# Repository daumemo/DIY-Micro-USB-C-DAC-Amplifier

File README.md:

# DIY-Micro-USB-C-DAC-Amplifier
A DIY headphone amplifier based on INA1620 and USB-C DAC

Here you will find all Hardware files for my DIY micro headphone amplifier.

More information you can find at my site: https://daumemo.com/diy-micro-usb-c-to-3-5mm-adapter-and-headphone-amplifier-part-4/

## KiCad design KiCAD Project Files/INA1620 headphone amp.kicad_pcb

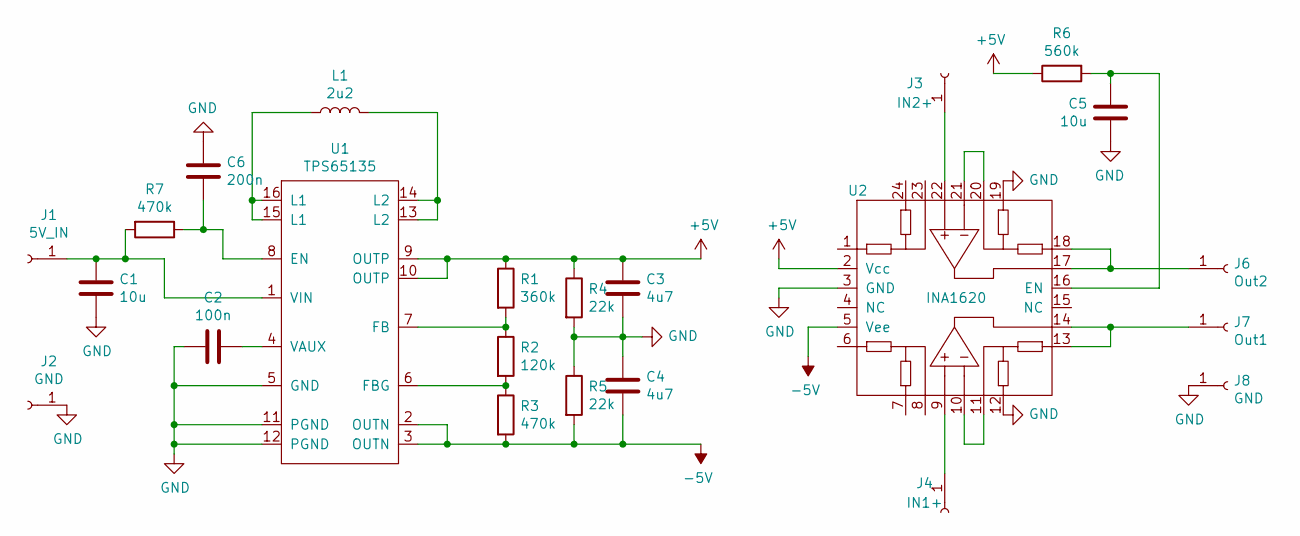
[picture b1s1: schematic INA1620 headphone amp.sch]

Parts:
C1, C5: 10u; C_0603_1608Metric
C2: 100n; C_0402_1005Metric
C3, C4: 4u7; C_0603_1608Metric
C6: 200n; C_0402_1005Metric
J1: 5V_IN; TestPoint_Pad_1.5x1.5mm
J2, J8: GND; TestPoint_Pad_1.5x1.5mm
J3: IN2+; TestPoint_Pad_1.5x1.5mm
J4: IN1+; TestPoint_Pad_1.5x1.5mm
J6: Out2; TestPoint_Pad_1.5x1.5mm
J7: Out1; TestPoint_Pad_1.5x1.5mm
L1: 2u2; L_Wuerth_MAPI-2512
R1: 360k; R_0402_1005Metric
R2: 120k; R_0402_1005Metric
R3, R7: 470k; R_0402_1005Metric
R4, R5: 22k; R_0402_1005Metric
R6: 560k; R_0603_1608Metric
U1: TPS65135; QFN-16-1EP_3x3mm_P0.5mm_EP1.7x1.7mm
U2: INA1620; QFN-24-1EP_4x4mm_P0.5mm_EP2.7x2.7mm

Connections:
+5V: C3.1, R1.1, R4.1, R6.1, U1.9 (OUTP), U1.10 (OUTP), U2.2 (Vcc)
-5V: C4.2, R3.2, R5.2, U1.2 (OUTN), U1.3 (OUTN), U2.5 (Vee)
GND: C1.2, C2.2, C3.2, C4.1, C5.2, C6.1, J2.1, J8.1, R4.2, R5.1, U1.5 (GND), U1.11 (PGND), U1.12 (PGND), U2.3 (GND), U2.12, U2.19
unnamed: C1.1, J1.1, R7.2, U1.1 (VIN)
unnamed: C2.1, U1.4 (VAUX)
unnamed: C5.1, R6.2, U2.16 (EN)
unnamed: C6.2, R7.1, U1.8 (EN)
unnamed: J3.1, U2.22
unnamed: J4.1, U2.9
unnamed: J6.1, U2.17, U2.18
unnamed: J7.1, U2.13, U2.14
unnamed: L1.1, U1.15 (L1), U1.16 (L1)
unnamed: L1.2, U1.13 (L2), U1.14 (L2)
unnamed: R1.2, R2.1, U1.7 (FB)
unnamed: R2.2, R3.1, U1.6 (FBG)
unnamed: U2.10, U2.11
unnamed: U2.20, U2.21

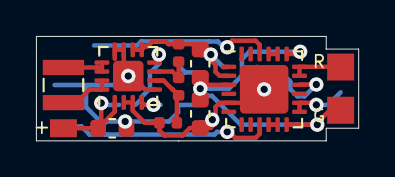
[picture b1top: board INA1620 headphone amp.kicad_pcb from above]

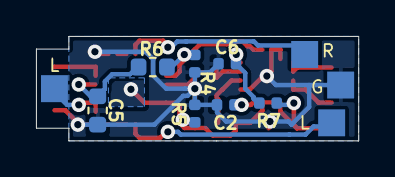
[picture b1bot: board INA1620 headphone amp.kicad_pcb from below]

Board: 2 copper layers, 17.9 x 5.8 mm, 23 parts (11 on the bottom side), 17 nets.

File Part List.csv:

Id;Designator;Package;Quantity;Designation;;
7;C1;C_0603_1608Metric;1;10u;;
8;C2;C_0402_1005Metric;1;100n;;
9;C3,C4;C_0603_1608Metric;2;4u7;;
10;C5;C_0603_1608Metric;1;10u;;
11;C6;C_0402_1005Metric;1;200n (220n);;
12;L1;L_Wuerth_MAPI-2512;1;2u2;;
13;R1;R_0402_1005Metric;1;360k;;
14;R2;R_0402_1005Metric;1;120k;;
15;R3;R_0402_1005Metric;1;470k;;
16;R4,R5;R_0402_1005Metric;2;22k;;
17;R7;R_0402_1005Metric;1;470k;;
18;U1;QFN-16-1EP_3x3mm_P0.5mm_EP1.7x1.7mm;1;TPS65135;;
19;U2;QFN-24-1EP_4x4mm_P0.5mm_EP2.7x2.7mm;1;INA1620;;
20;R6;R_0603_1608Metric;1;560k;;
;;;;;;
;;;;;;
;;;;;;
Parts not on the board:;;;;;;
1;USB 4 wire cable;;;;;
2;USB-C DAC;https://s.click.aliexpress.com/e/_AY67DI;;Or Alternative:;;https://s.click.aliexpress.com/e/_ANoKTm
3;3.5 mm Jack;https://s.click.aliexpress.com/e/_9x1f60;;;;

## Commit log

2021-09-15 Initial update
2021-09-15 Grammar mistakes
